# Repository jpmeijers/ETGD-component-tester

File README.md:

# ETGD-component-tester
ETGD component tester schematic and PC board

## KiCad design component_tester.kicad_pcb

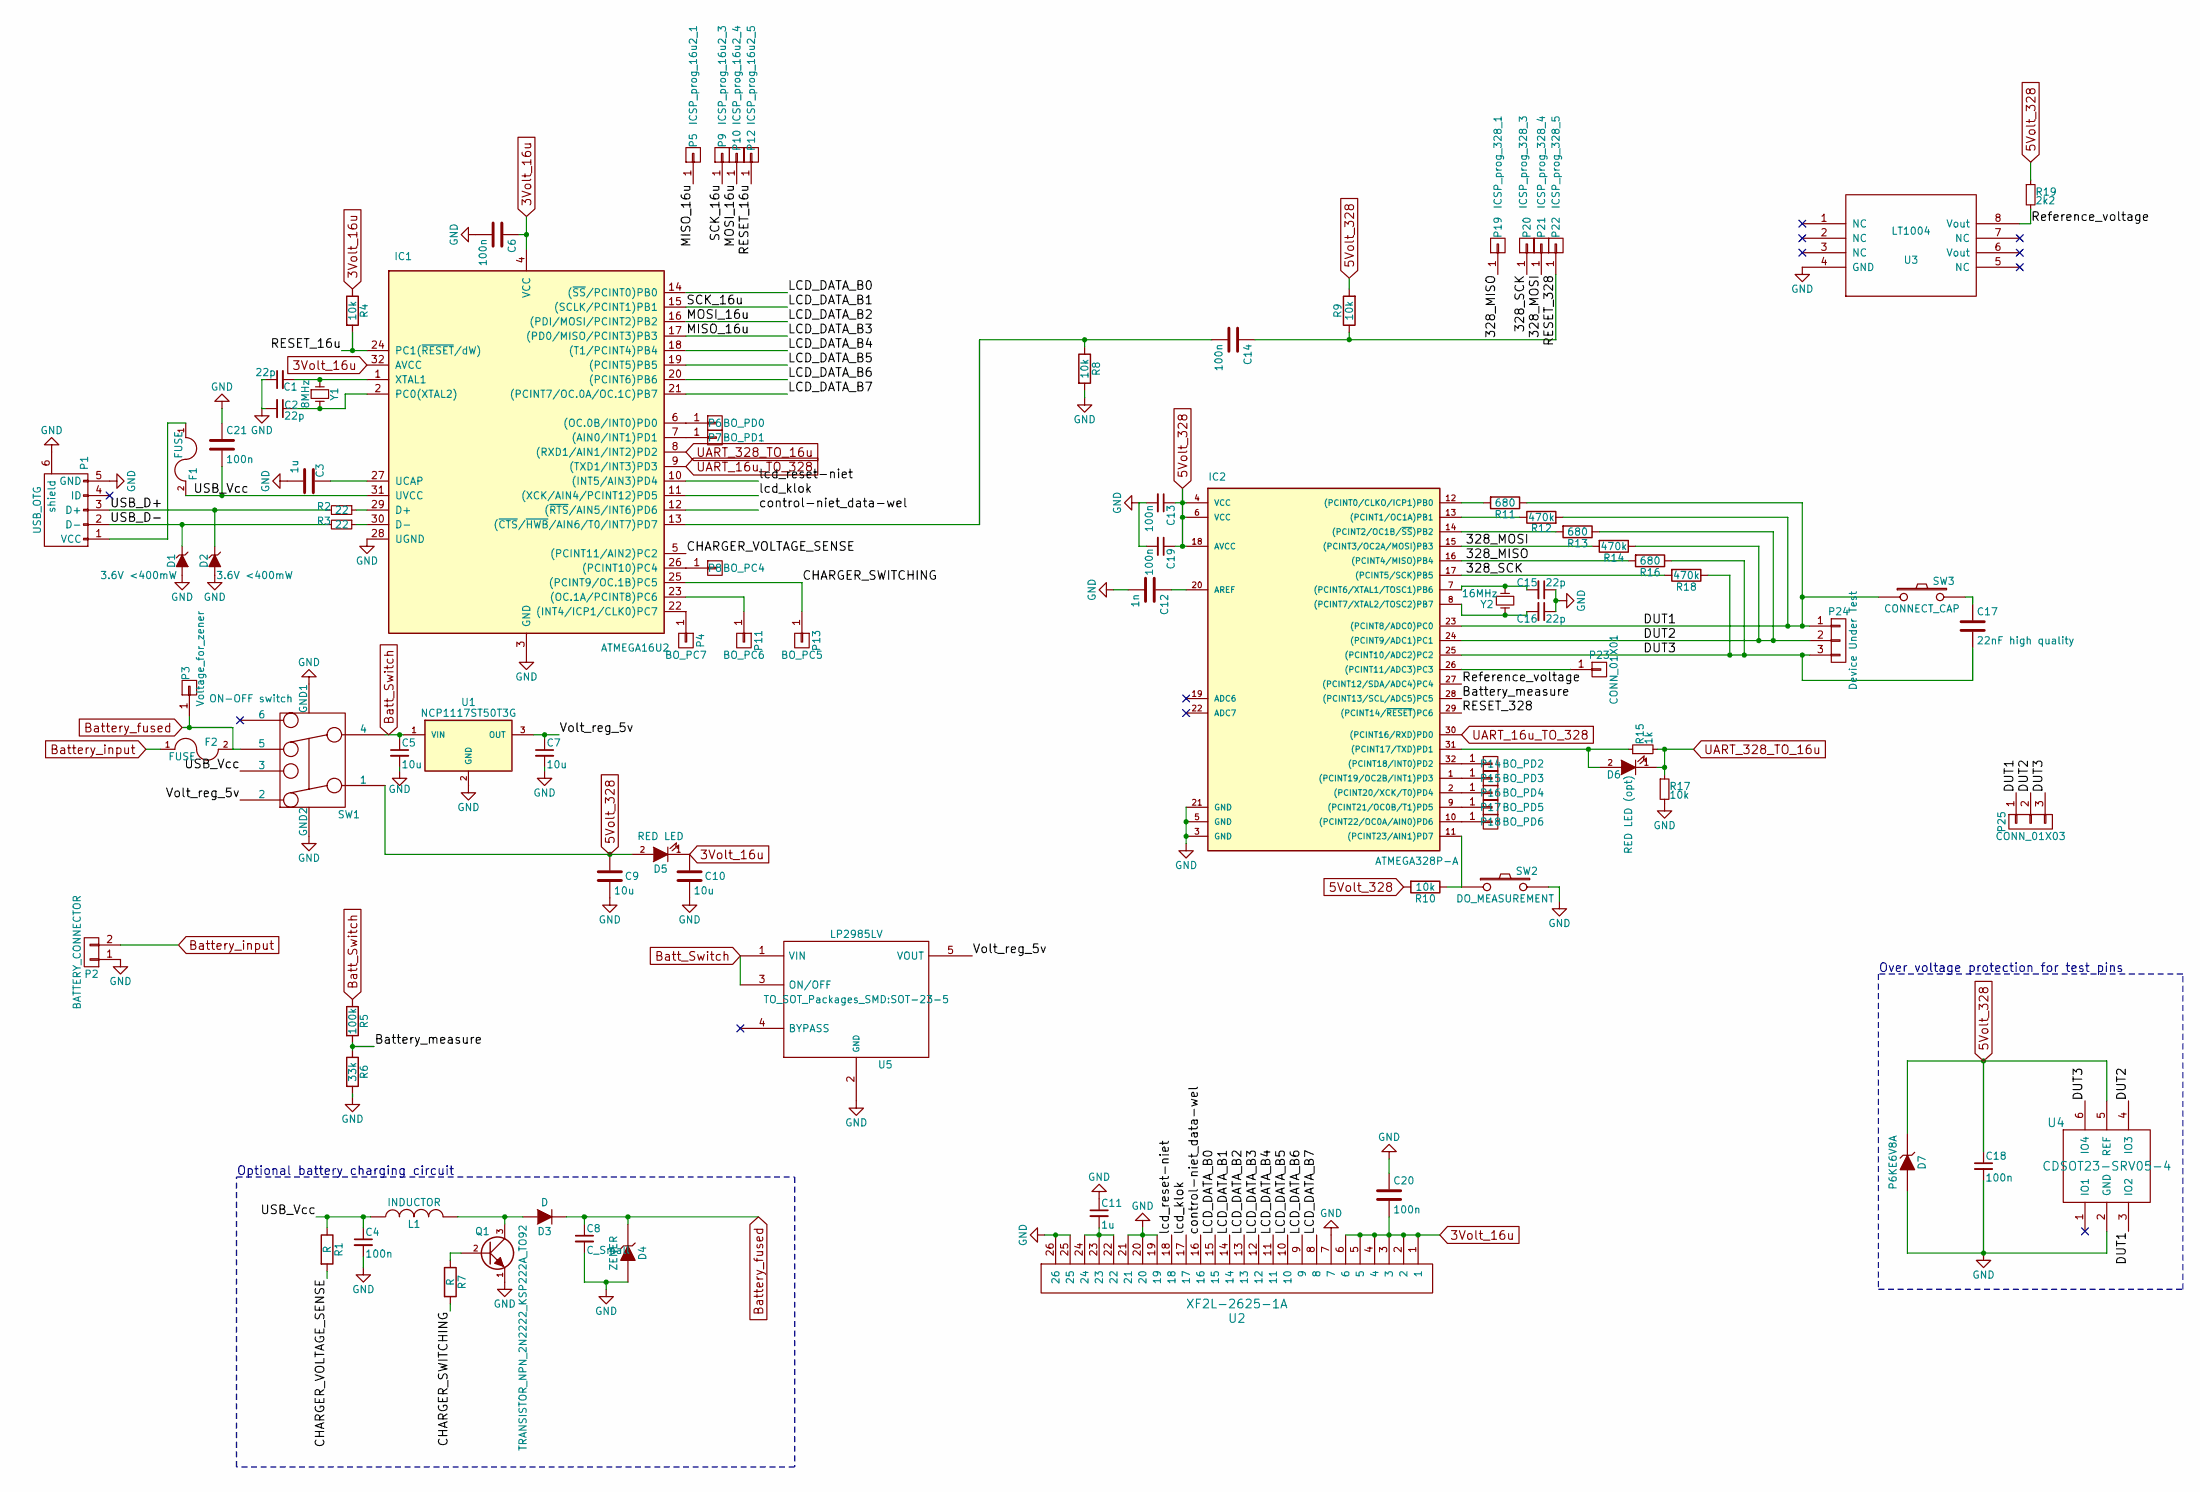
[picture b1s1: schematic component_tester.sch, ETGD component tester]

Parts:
C1, C2, C15, C16: 22p; C_0805_HandSoldering
C3, C11: 1u; C_0805_HandSoldering
C4, C6, C13, C14, C18, C19, C20, C21: 100n; C_0805_HandSoldering
C5, C7, C9, C10: 10u; C_0805_HandSoldering
C8: C_Small; C_0805_HandSoldering
C12: 1n; C_0805_HandSoldering
C17: 22nF high quality; C_1206_HandSoldering
D1, D2: 3.6V <400mW; SOT-23
D3: D; SOT-23
D4: ZENER; SOT-23
D5: RED LED; FOON_LED
D6: RED LED (opt); FOON_LED
D7: P6KE6V8A; SOT-23
F1, F2: FUSE; R_0805_HandSoldering
IC1: ATMEGA16U2; TQFP-32_7x7mm_Pitch0.8mm
IC2: ATMEGA328P-A; TQFP-32_7x7mm_Pitch0.8mm
L1: INDUCTOR; SELF-WE-PD3S
P1: USB_OTG; USB_Micro-B
P2: BATTERY_CONNECTOR; Pin_Header_Straight_1x02
P3: Voltage_for_zener; Pin_Header_Straight_1x01
P4: BO_PC7; Pin_Header_Straight_1x01
P5: ICSP_prog_16u2_1; Pin_Header_Straight_1x01
P6: BO_PD0; Pin_Header_Straight_1x01
P7: BO_PD1; Pin_Header_Straight_1x01
P8: BO_PC4; Pin_Header_Straight_1x01
P9: ICSP_prog_16u2_3; Pin_Header_Straight_1x01
P10: ICSP_prog_16u2_4; Pin_Header_Straight_1x01
P11: BO_PC6; Pin_Header_Straight_1x01
P12: ICSP_prog_16u2_5; Pin_Header_Straight_1x01
P13: BO_PC5; Pin_Header_Straight_1x01
P14: BO_PD2; Pin_Header_Straight_1x01
P15: BO_PD3; Pin_Header_Straight_1x01
P16: BO_PD4; Pin_Header_Straight_1x01
P17: BO_PD5; Pin_Header_Straight_1x01
P18: BO_PD6; Pin_Header_Straight_1x01
P19: ICSP_prog_328_1; Pin_Header_Straight_1x01
P20: ICSP_prog_328_3; Pin_Header_Straight_1x01
P21: ICSP_prog_328_4; Pin_Header_Straight_1x01
P22: ICSP_prog_328_5; Pin_Header_Straight_1x01
P23: CONN_01X01; Pin_Header_Straight_1x01
P24: Device Under Test; CONN_DUT
P25: CONN_01X03; CONN_DUT_SMD
Q1: TRANSISTOR_NPN_2N2222_KSP222A_TO92; TO-92_Inline_Narrow_Oval
R1, R7: R; R_0805_HandSoldering
R2, R3: 22; R_0805_HandSoldering
R4, R8, R9, R10, R17: 10k; R_0805_HandSoldering
R5: 100k; R_0805_HandSoldering
R6: 33k; R_0805_HandSoldering
R11, R13, R16: 680; R_0805_HandSoldering
R12, R14, R18: 470k; R_0805_HandSoldering
R15: 1k; R_0805_HandSoldering
R19: 2k2; R_0805_HandSoldering
SW1: ON-OFF switch; SWITCH_DPDT_SLIDE_OS202011MA0QN1
SW2: DO_MEASUREMENT; SW_PUSH_SMALL
SW3: CONNECT_CAP; SW_PUSH_SMALL
U1: NCP1117ST50T3G; SOT-223
U2: XF2L-2625-1A; CONN_FPC_FFC_0.5mm_26PIN_DRAWER_BOTTOM
U3: LT1004; SOIC-8-N
U4: CDSOT23-SRV05-4; SOT-23-6_Handsoldering
U5: LP2985LV; SOT-23-5
Y1: 8MHz; Crystal_HC49-U_Vertical
Y2: 16MHz; Crystal_HC49-U_Vertical

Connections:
3Volt_16u: C6.1, C10.1, C20.2, D5.1 (K), IC1.4 (VCC), IC1.32 (AVCC), R4.1, U2.1, U2.2, U2.3, U2.4, U2.5, U2.6
5Volt_328: C9.1, C13.1, C18.1, C19.1, D5.2 (A), D7.1 (K), IC2.4 (VCC), IC2.6 (VCC), IC2.18 (AVCC), R9.2, R10.2, R19.1, SW1.1, U4.5 (REF)
/328_MISO: IC2.16 ((PCINT4/MISO)PB4), P19.1, R16.2
/328_MOSI: IC2.15 ((PCINT3/OC2A/MOSI)PB3), P21.1, R14.2
/328_SCK: IC2.17 ((PCINT5/SCK)PB5), P20.1, R18.2
/Battery_measure: IC2.28 ((PCINT13/SCL/ADC5)PC5), R5.2, R6.1
/CHARGER_SWITCHING: IC1.25 ((PCINT9/OC.1B)PC5), P13.1, R7.2
/CHARGER_VOLTAGE_SENSE: IC1.5 ((PCINT11/AIN2)PC2), R1.2
/DUT1: IC2.23 ((PCINT8/ADC0)PC0), P24.1, P25.1, R11.1, R12.2, SW3.1, U4.3 (IO2)
/DUT2: IC2.24 ((PCINT9/ADC1)PC1), P24.2, P25.2, R13.1, R14.1, U4.4 (IO3)
/DUT3: C17.2, IC2.25 ((PCINT10/ADC2)PC2), P24.3, P25.3, R16.1, R18.1, U4.6 (IO4)
/LCD_DATA_B0: IC1.14 ((~SS~/PCINT0)PB0), U2.15
/LCD_DATA_B1: IC1.15 ((SCLK/PCINT1)PB1), P9.1, U2.14
/LCD_DATA_B2: IC1.16 ((PDI/MOSI/PCINT2)PB2), P10.1, U2.13
/LCD_DATA_B3: IC1.17 ((PD0/MISO/PCINT3)PB3), P5.1, U2.12
/LCD_DATA_B4: IC1.18 ((T1/PCINT4)PB4), U2.11
/LCD_DATA_B5: IC1.19 ((PCINT5)PB5), U2.10
/LCD_DATA_B6: IC1.20 ((PCINT6)PB6), U2.9
/LCD_DATA_B7: IC1.21 ((PCINT7/OC.0A/OC.1C)PB7), U2.8
/RESET_16u: IC1.24 (PC1(~RESET~/dW)), P12.1, R4.2
/RESET_328: C14.1, IC2.29 ((PCINT14/~RESET~)PC6), P22.1, R9.1
/Reference_voltage: IC2.27 ((PCINT12/SDA/ADC4)PC4), R19.2, U3.8 (Vout)
/USB_D+: D2.1 (K), P1.3 (D+), R2.2
/USB_D-: D1.1 (K), P1.2 (D-), R3.2
/USB_Vcc: C4.1, C21.2, F1.2, IC1.31 (UVCC), L1.1, R1.1, SW1.3
/Volt_reg_5v: C7.1, SW1.2, U1.3 (OUT), U5.5 (VOUT)
/control-niet_data-wel: IC1.12 ((~RTS~/AIN5/INT6)PD6), U2.16
/lcd_klok: IC1.11 ((XCK/AIN4/PCINT12)PD5), U2.17
/lcd_reset-niet: IC1.10 ((INT5/AIN3)PD4), U2.18
Batt_Switch: C5.1, R5.1, SW1.4, U1.1 (VIN), U5.1 (VIN), U5.3 (ON/OFF)
Battery_fused: C8.1, D3.1 (K), D4.1 (K), F2.2, P3.1, SW1.5
Battery_input: F2.1, P2.2
GND: C1.1, C2.2, C3.2, C4.2, C5.2, C6.2, C7.2, C8.2, C9.2, C10.2, C11.1, C12.2, C13.2, C15.1, C16.1, C18.2, C19.2, C20.1, C21.1, D1.2 (A), D2.2 (A), D4.2 (A), D7.2 (A), IC1.3 (GND), IC1.28 (UGND), IC2.3 (GND), IC2.5 (GND), IC2.21 (GND), P1.5 (GND), P1.6 (shield), P2.1, Q1.1 (E), R6.2, R8.2, R17.2, SW1.7 (GND1), SW1.8 (GND2), SW2.2, U1.2 (GND), U1.4, U2.7, U2.19, U2.20, U2.21, U2.25, U2.26, U3.4 (GND), U4.2 (GND), U5.2 (GND)
unnamed: C1.2, IC1.1 (XTAL1), Y1.1
unnamed: C2.1, IC1.2 (PC0(XTAL2)), Y1.2
unnamed: C3.1, IC1.27 (UCAP)
unnamed: C11.2, U2.22, U2.23, U2.24
unnamed: C12.1, IC2.20 (AREF)
unnamed: C14.2, IC1.13 ((~CTS~/~HWB~/AIN6/T0/INT7)PD7), R8.1
unnamed: C15.2, IC2.7 ((PCINT6/XTAL1/TOSC1)PB6), Y2.1
unnamed: C16.2, IC2.8 ((PCINT7/XTAL2/TOSC2)PB7), Y2.2
unnamed: C17.1, SW3.2
unnamed: D3.2 (A), L1.2, Q1.3 (C)
unnamed: D6.2 (A), IC2.31 ((PCINT17/TXD)PD1), R15.1
unnamed: F1.1, P1.1 (VCC)
unnamed: IC1.6 ((OC.0B/INT0)PD0), P6.1
unnamed: IC1.7 ((AIN0/INT1)PD1), P7.1
unnamed: IC1.22 ((INT4/ICP1/CLK0)PC7), P4.1
unnamed: IC1.23 ((OC.1A/PCINT8)PC6), P11.1
unnamed: IC1.26 ((PCINT10)PC4), P8.1
unnamed: IC1.29 (D+), R2.1
unnamed: IC1.30 (D-), R3.1
unnamed: IC2.1 ((PCINT19/OC2B/INT1)PD3), P15.1
unnamed: IC2.2 ((PCINT20/XCK/T0)PD4), P16.1
unnamed: IC2.9 ((PCINT21/OC0B/T1)PD5), P17.1
unnamed: IC2.10 ((PCINT22/OC0A/AIN0)PD6), P18.1
unnamed: IC2.11 ((PCINT23/AIN1)PD7), R10.1, SW2.1
unnamed: IC2.12 ((PCINT0/CLKO/ICP1)PB0), R11.2
unnamed: IC2.13 ((PCINT1/OC1A)PB1), R12.1
unnamed: IC2.14 ((PCINT2/OC1B/~SS~)PB2), R13.2
unnamed: IC2.26 ((PCINT11/ADC3)PC3), P23.1
unnamed: IC2.32 ((PCINT18/INT0)PD2), P14.1
unnamed: Q1.2 (B), R7.1
UART_16u_TO_328: IC1.9 ((TXD1/INT3)PD3), IC2.30 ((PCINT16/RXD)PD0)
UART_328_TO_16u: D6.1 (K), IC1.8 ((RXD1/AIN1/INT2)PD2), R15.2, R17.1

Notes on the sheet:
Optional battery charging circuit
Over voltage protection for test pins

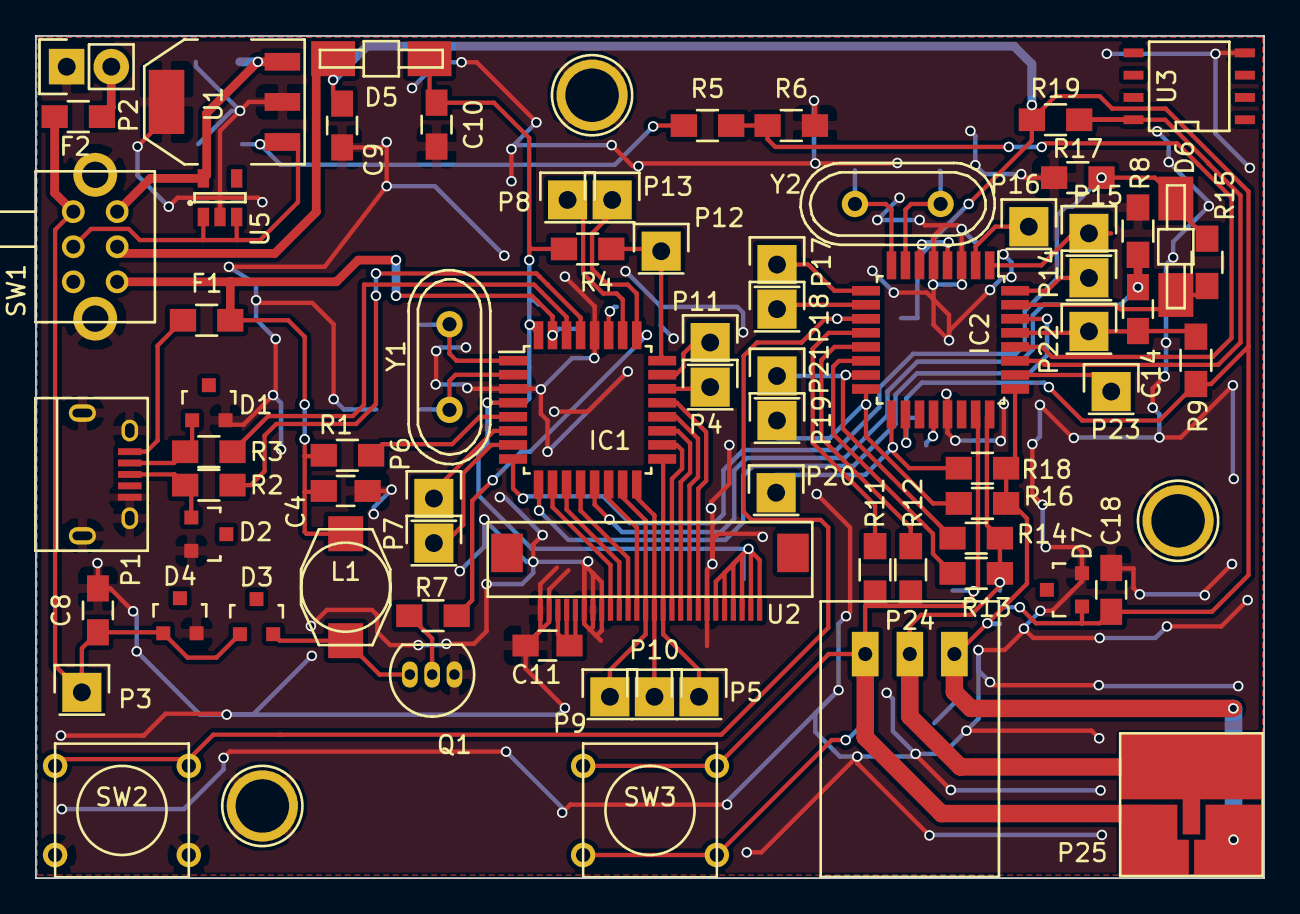
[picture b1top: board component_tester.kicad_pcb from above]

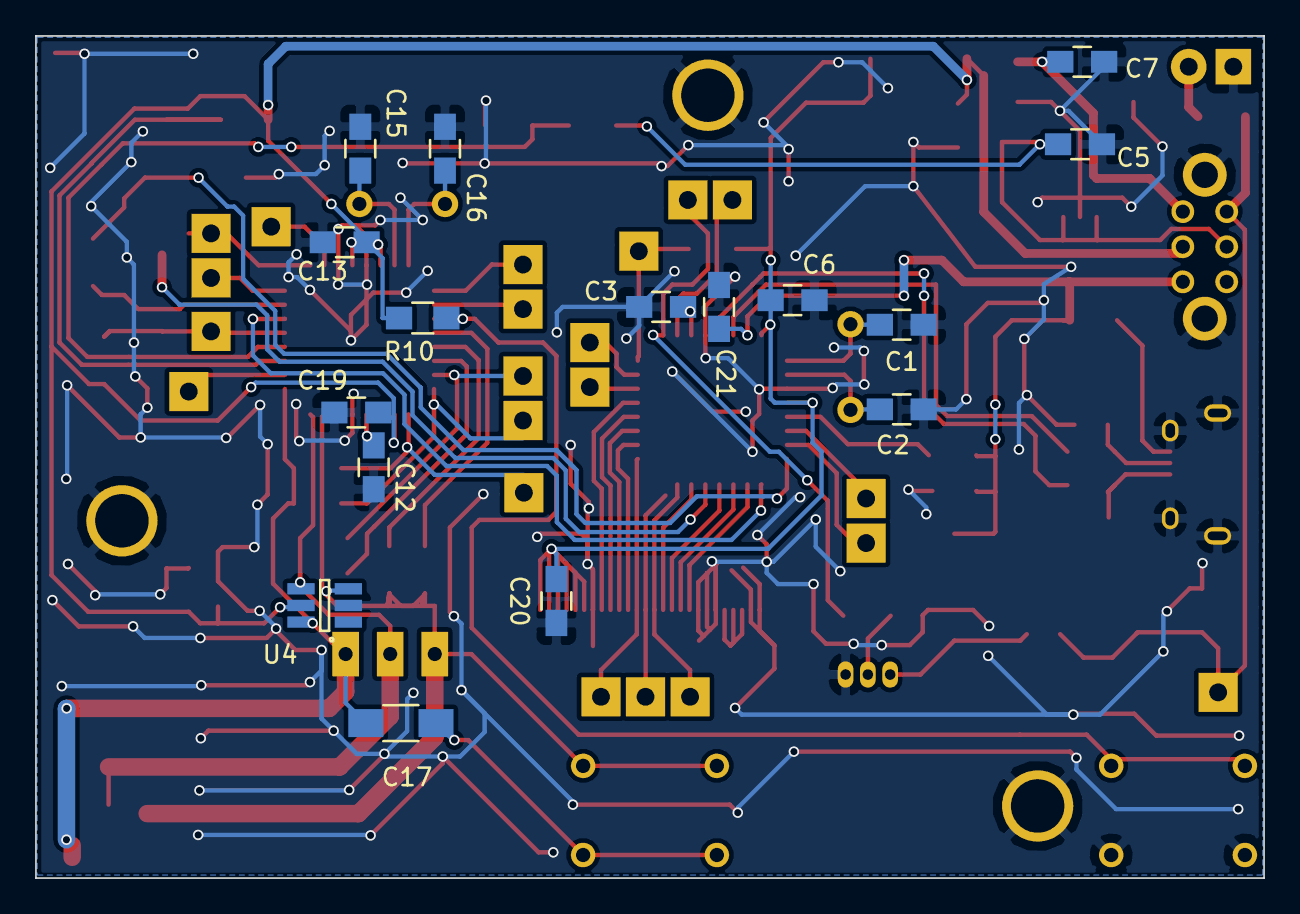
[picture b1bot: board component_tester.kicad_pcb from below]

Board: 2 copper layers, 70.0 x 48.0 mm, 88 parts (16 on the bottom side), 65 nets.

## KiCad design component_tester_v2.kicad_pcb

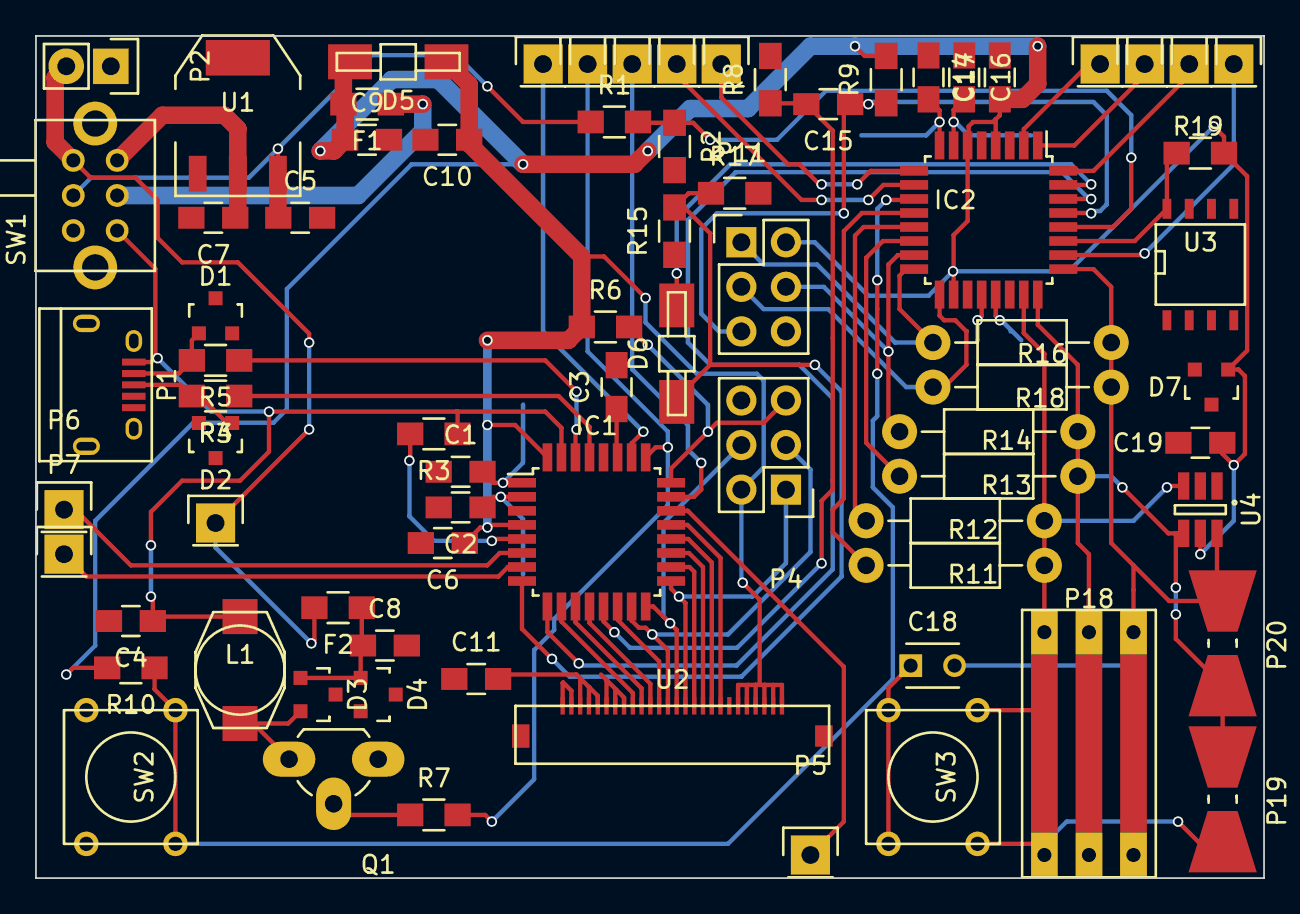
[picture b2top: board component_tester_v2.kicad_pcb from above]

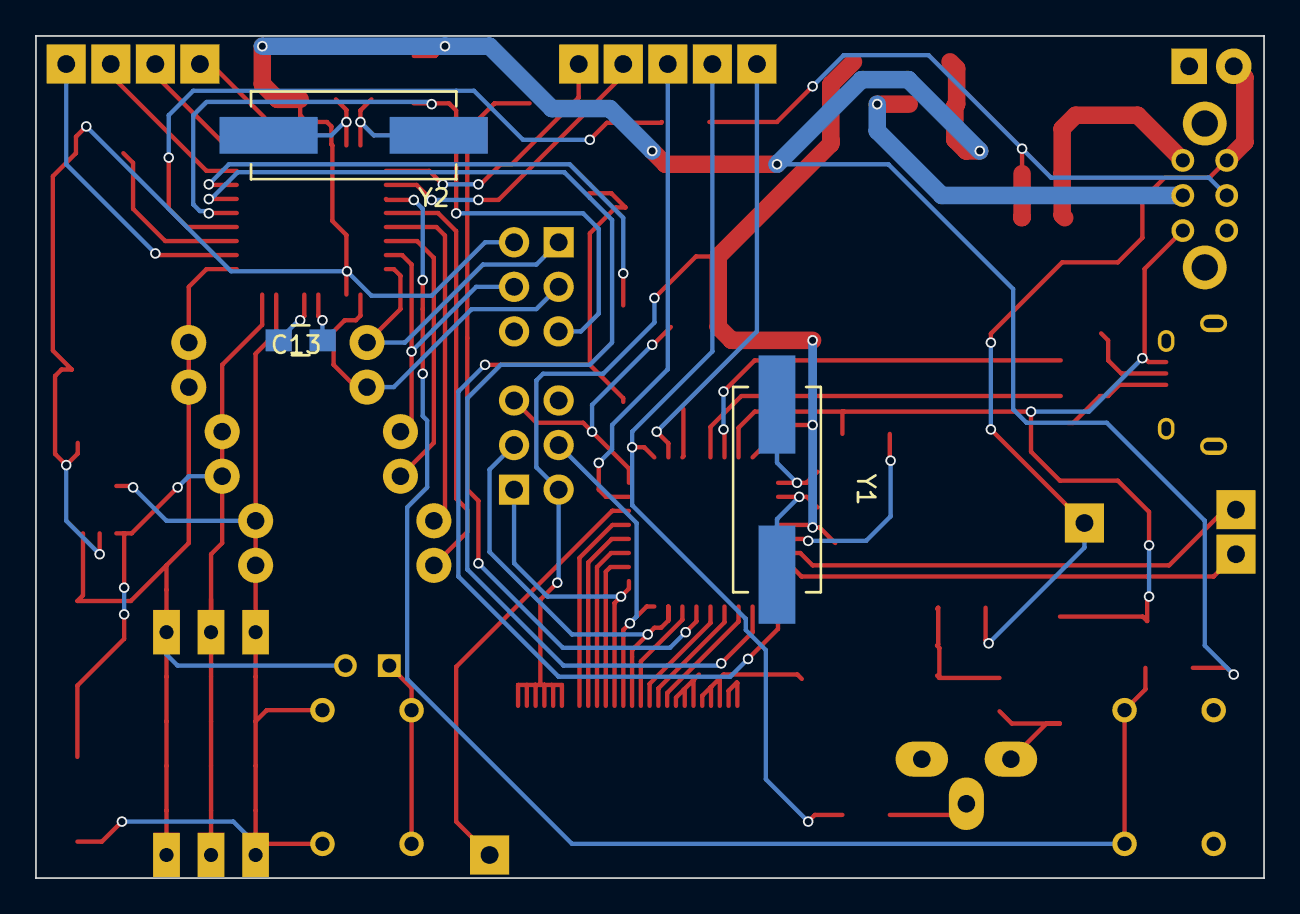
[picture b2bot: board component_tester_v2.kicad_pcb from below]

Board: 2 copper layers, 70.0 x 48.0 mm, 79 parts (3 on the bottom side), 65 nets.

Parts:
C1, C2: 22p; C_0805_HandSoldering
C3: 1uF; C_0805_HandSoldering
C4, C6, C14, C15, C19: 100n; C_0805_HandSoldering
C5, C7: 10u; C_0805_HandSoldering
C8: C_Small; C_0805_HandSoldering
C9, C10: 10uF; C_0805_HandSoldering
C11: 1u; C_0805_HandSoldering
C13: 1n; C_0805_HandSoldering
C16, C17: 22pF; C_0805_HandSoldering
C18: 22nF high quality; C_Disc_D3_P2.5
D1, D2: 3.6V <400mW; SOT-23
D3: D; SOT-23
D4: ZENER; SOT-23
D5: RED LED; FOON_LED
D6: RED LED (opt); FOON_LED
D7: P6KE6V8A; SOT-23
F1, F2: FUSE; R_0805_HandSoldering
IC1: ATMEGA16U2; TQFP-32_7x7mm_Pitch0.8mm
IC2: ATMEGA328P-A; TQFP-32_7x7mm_Pitch0.8mm
L1: INDUCTOR; SELF-WE-PD3S
P1: USB_OTG; USB_Micro-B
P2: BATTERY_CONNECTOR; Pin_Header_Straight_1x02
P3: Voltage_for_zener; Pin_Header_Straight_1x01
P4: ICSP_prog_16u2; Pin_Header_Straight_2x03
P5: BO_PC7; Pin_Header_Straight_1x01
P6: BO_PD0; Pin_Header_Straight_1x01
P7: BO_PD1; Pin_Header_Straight_1x01
P8: BO_PC4; Pin_Header_Straight_1x01
P9: BO_PC6; Pin_Header_Straight_1x01
P10: BO_PC5; Pin_Header_Straight_1x01
P11: ICSP_prog_328p; Pin_Header_Straight_2x03
P12: BO_PD2; Pin_Header_Straight_1x01
P13: BO_PD3; Pin_Header_Straight_1x01
P14: BO_PD4; Pin_Header_Straight_1x01
P15: BO_PD5; Pin_Header_Straight_1x01
P16: BO_PD6; Pin_Header_Straight_1x01
P17: CONN_01X01; Pin_Header_Straight_1x01
P18: Device Under Test; CONN_DUT
P19: DUT_SMD_1_2; Resistor_SMDuniversal_0805to2512_HandSoldering
P20: DUT_SMD_2_3; Resistor_SMDuniversal_0805to2512_HandSoldering
Q1: TRANSISTOR_NPN_2N2222_KSP222A_TO92; TO-92_Rugged
R1: 100k; R_0805_HandSoldering
R2: 33k; R_0805_HandSoldering
R3, R7: R; R_0805_HandSoldering
R4, R5: 22; R_0805_HandSoldering
R6, R8, R9, R10, R17: 10k; R_0805_HandSoldering
R11, R13, R16: 680; Resistor_Horizontal_RM10mm
R12, R14, R18: 470k; Resistor_Horizontal_RM10mm
R15: 1k; R_0805_HandSoldering
R19: 2k2; R_0805_HandSoldering
SW1: ON-OFF switch; SWITCH_DPDT_SLIDE_OS202011MA0QN1
SW2: DO_MEASUREMENT; SW_PUSH_SMALL
SW3: CONNECT_CAP; SW_PUSH_SMALL
U1: NCP1117ST50T3G; SOT-223
U2: XF2L-2625-1A
U3: LT1004; SOIC-8-N
U4: CDSOT23-SRV05-4; SOT-23-6_Handsoldering
Y1: 8MHz; Crystal_HC49-SD_SMD
Y2: 16MHz; Crystal_HC49-SD_SMD

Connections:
3Volt_16u: C6.1, C10.1, D5.1, IC1.4, IC1.32, P4.2, R6.1, U2.1, U2.2, U2.3, U2.4, U2.5, U2.6
5Volt_328: C9.1, C14.1, C19.1, D5.2, D7.1, F1.2, IC2.4, IC2.6, IC2.18, P11.2, R9.2, R10.2, R19.1, U4.5
/Battery_measure: IC2.28, R1.2, R2.1
/CHARGER_SWITCHING: IC1.25, P10.1, R7.2
/CHARGER_VOLTAGE_SENSE: IC1.5, R3.2
/DUT1: IC2.23, P18.1, P19.2, R11.1, R12.2, SW3.1, U4.3
/DUT2: IC2.24, P18.2, P19.1, P20.2, R13.1, R14.1, U4.4
/DUT3: C18.2, IC2.25, P18.3, P20.1, R16.1, R18.1, U4.6
/LCD_DATA_B0: IC1.14, U2.15
/LCD_DATA_B1: IC1.15, P4.3, U2.14
/LCD_DATA_B2: IC1.16, P4.4, U2.13
/LCD_DATA_B3: IC1.17, P4.1, U2.12
/LCD_DATA_B4: IC1.18, U2.11
/LCD_DATA_B5: IC1.19, U2.10
/LCD_DATA_B6: IC1.20, U2.9
/LCD_DATA_B7: IC1.21, U2.8
/RESET_16u: IC1.24, P4.5, R6.2
/RESET_328: C15.1, IC2.29, P11.5, R9.1
/Reference_voltage: IC2.27, R19.2, U3.8
/USB_D+: D2.1, P1.3, R4.2
/USB_D-: D1.1, P1.2, R5.2
/USB_Vcc: C4.1, IC1.31, L1.1, P1.1, R3.1, SW1.3
/Volt_reg_5v: C7.1, SW1.2, U1.2
/control-niet_data-wel: IC1.12, U2.16
/lcd_klok: IC1.11, U2.17
/lcd_reset-niet: IC1.10, U2.18
Batt_Switch: C5.1, R1.1, SW1.4, U1.3
Battery_input: F2.2, P2.2, P3.1, SW1.5
GND: C1.1, C2.2, C3.2, C4.2, C5.2, C6.2, C7.2, C8.2, C9.2, C10.2, C11.1, C13.2, C14.2, C16.1, C17.1, C19.2, D1.2, D2.2, D4.2, D7.2, IC1.3, IC1.28, IC2.3, IC2.5, IC2.21, P1.5, P1.6, P2.1, P4.6, P11.6, Q1.1, R2.2, R8.2, R17.2, SW1.7, SW1.8, SW2.2, U1.1, U2.7, U2.19, U2.20, U2.21, U2.25, U2.26, U3.4, U4.2
unnamed: C1.2, IC1.1, Y1.1
unnamed: C2.1, IC1.2, Y1.2
unnamed: C3.1, IC1.27
unnamed: C8.1, D3.1, D4.1, F2.1
unnamed: C11.2, U2.22, U2.23, U2.24
unnamed: C13.1, IC2.20
unnamed: C15.2, IC1.13, R8.1
unnamed: C16.2, IC2.7, Y2.1
unnamed: C17.2, IC2.8, Y2.2
unnamed: C18.1, SW3.2
unnamed: D3.2, L1.2, Q1.3
unnamed: D6.2, IC2.31, R15.1
unnamed: F1.1, SW1.1
unnamed: IC1.6, P6.1
unnamed: IC1.7, P7.1
unnamed: IC1.22, P5.1
unnamed: IC1.23, P9.1
unnamed: IC1.26, P8.1
unnamed: IC1.29, R4.1
unnamed: IC1.30, R5.1
unnamed: IC2.1, P13.1
unnamed: IC2.2, P14.1
unnamed: IC2.9, P15.1
unnamed: IC2.10, P16.1
unnamed: IC2.11, R10.1, SW2.1
unnamed: IC2.12, R11.2
unnamed: IC2.13, R12.1
unnamed: IC2.14, R13.2
unnamed: IC2.15, P11.4, R14.2
unnamed: IC2.16, P11.1, R16.2
unnamed: IC2.17, P11.3, R18.2
unnamed: IC2.26, P17.1
unnamed: IC2.32, P12.1
unnamed: Q1.2, R7.1
UART_16u_TO_328: IC1.9, IC2.30
UART_328_TO_16u: D6.1, IC1.8, R15.2, R17.1

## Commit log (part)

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2016-06-15 Schematic version 1
2016-06-17 PCB drawn
2016-06-19 PCB layout changes
2016-06-19 Updated library components
2016-06-19 Updated schematic. New PCB layout.
2016-06-22 Version 3 of the PCB
2016-06-22 Resonator Capacitor closer. A lot of GND vias.
2016-06-22 Added extra vias. Add cap on LCD power.
2016-06-22 Added screw holes
2016-06-25 Fix capacitor values Added Vusb cap, fix unconnected nets, better grounding.
2016-06-25 Move component references on silkscreen to be more readable.
2016-06-25 Added voltage regulator option
2016-06-26 Added the possibility of using a different LDO voltage regulator.
2016-06-27 Moved USB port slightly further away from switch. As uploaded to DirtyPCBs
